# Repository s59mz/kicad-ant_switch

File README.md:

# kicad-ant_switch
HF Antenna Switch

Schematic:
[ant_switch.pdf](PL_switch.pdf)

BOM:
[ant_switch.csv](PL_switch.csv)

Gerbers:
[gerbers.zip](https://github.com/s59mz/kicad-ant_switch/raw/main/gerbers.zip)

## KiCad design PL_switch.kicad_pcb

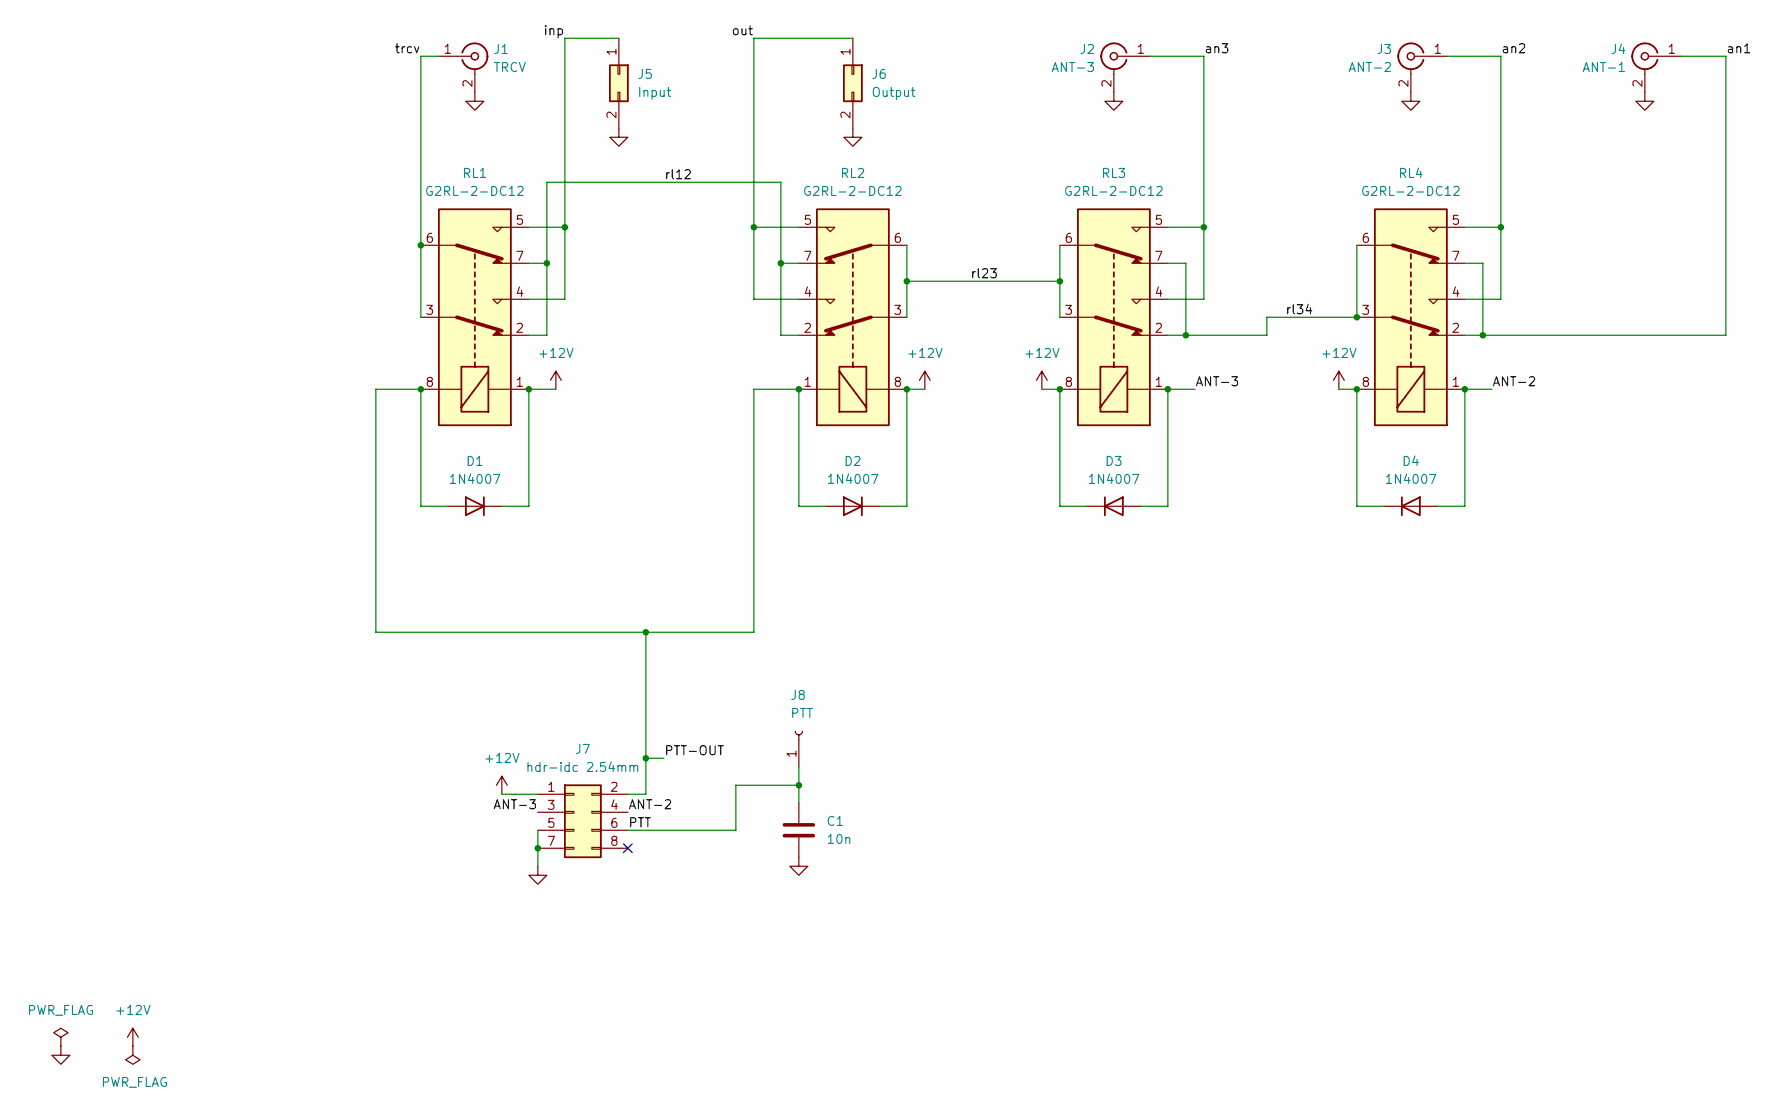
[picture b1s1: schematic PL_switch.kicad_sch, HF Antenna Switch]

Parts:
C1: 10n; C_0805_2012Metric_Pad1.18x1.45mm_HandSolder
D1, D2, D3, D4: 1N4007; D_SMB
J1: TRCV; SO-239
J2: ANT-3; SO-239
J3: ANT-2; SO-239
J4: ANT-1; SO-239
J5: Input; Conn_2x1
J6: Output; Conn_2x1
J7: hdr-idc 2.54mm; PinHeader_2x04_P2.54mm_Vertical
J8: PTT; Conn_1x1
RL1, RL2, RL3, RL4: G2RL-2-DC12; Relay_DPDT_Omron_G2RL

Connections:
+12V: D1.1 (K), D2.1 (K), D3.1 (K), D4.1 (K), J7.1, RL1.1, RL2.8, RL3.8, RL4.8
/ANT-2: D4.2 (A), J7.4, RL4.1
/ANT-3: D3.2 (A), J7.3, RL3.1
/PTT: C1.1, J7.6, J8.1
/PTT-OUT: D1.2 (A), D2.2 (A), J7.2, RL1.8, RL2.1
/an1: J4.1 (In), RL4.2, RL4.7
/an2: J3.1 (In), RL4.4, RL4.5
/an3: J2.1 (In), RL3.4, RL3.5
/inp: J5.1, RL1.4, RL1.5
/out: J6.1, RL2.4, RL2.5
/rl12: RL1.2, RL1.7, RL2.2, RL2.7
/rl23: RL2.3, RL2.6, RL3.3, RL3.6
/rl34: RL3.2, RL3.7, RL4.3, RL4.6
/trcv: J1.1 (In), RL1.3, RL1.6
GND: C1.2, J1.2 (Ext), J2.2 (Ext), J3.2 (Ext), J4.2 (Ext), J5.2, J6.2, J7.5, J7.7

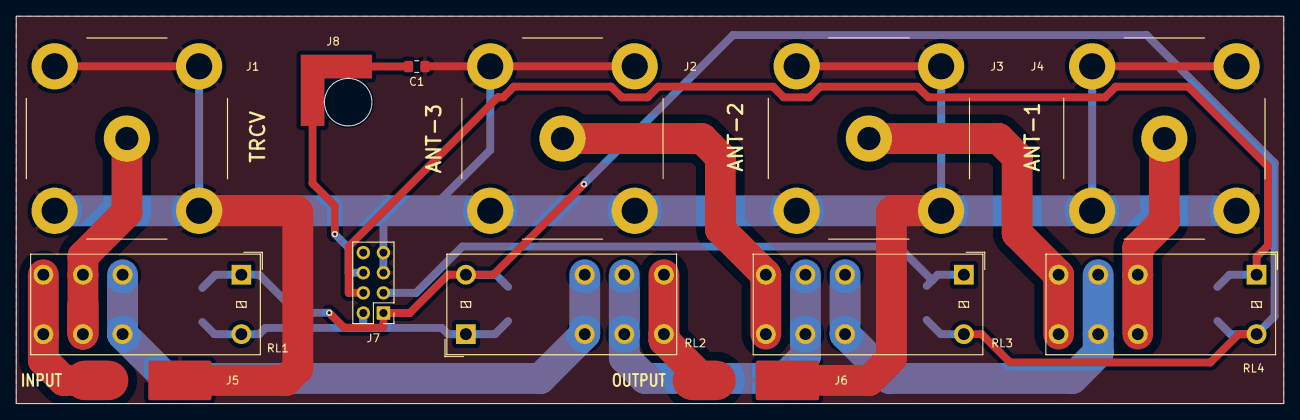
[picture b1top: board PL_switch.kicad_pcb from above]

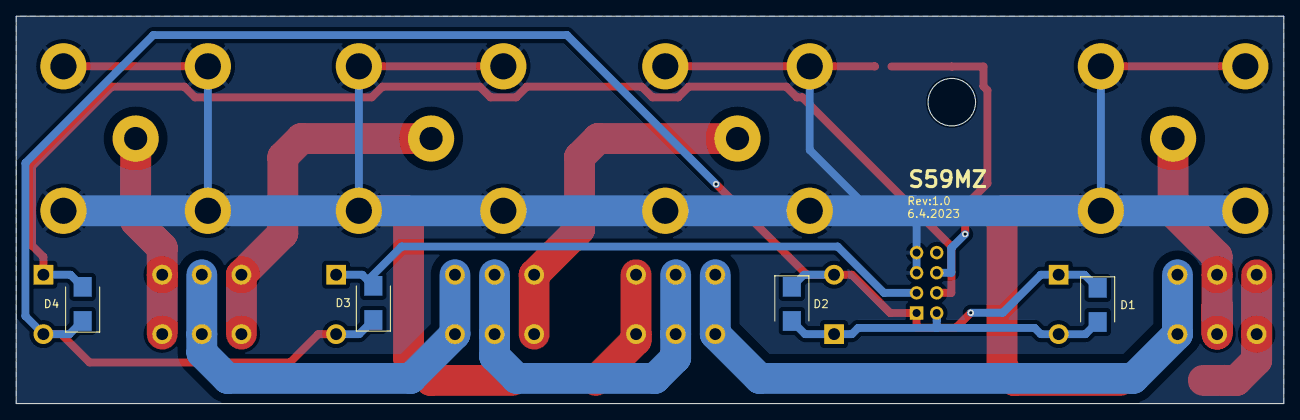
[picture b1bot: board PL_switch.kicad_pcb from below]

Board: 2 copper layers, 160.0 x 48.9 mm, 17 parts (4 on the bottom side), 15 nets.
